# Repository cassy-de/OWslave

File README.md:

# OWslave
OneWire Slave DIY Module

 ATtiny 25, intern 8MHz
 PB4 als Autoincrement-Counters.A, low-aktiv (Pegel), alle 10 Sekunden ein Count
 PB3 ist abgehängt von Counters.B, dafür machen PB0 und PB1 den I2C-Bus für den SRF02 auf 

 lfuse 62
 hfuse DF
 efuse FF

-------------
Zur Firmware:
Die I2C-Libs werden zusätzlich eingebunden, die I2C-Adresse des SRF02 ist fix 0xE0, er wird mit cm als Rückgabewert programmiert. Die Interrupts von
PB3 und PB4 sind disabled, denn PB3 (Counters.B) wird nicht benötigt (ist Messwert des SRF02), und PB4 (Counters.A) wird in der main{} gepollt, dann 10 Sekunden Pause und wieder von vorne, also eigentlich straightforward gelöst. Die I2C-Routine sind atomar gesetzt, dass hier kein IRQ dazwischenfunkt. Somit kann es passieren, dass u.U. der OWFS/OWserver das Device nicht erreicht. Aber lieber in FHEM einen alten Messwert fortschreiben, als einen definitiv falschen eintragen. Achso, in der ISR sind die beiden Increments gelöscht. Und die Extra-Inits für den ATtiny2313 habe ich gleich aus dem Quellcode geschmissen, somit liest es sich etwas leichter.

-------------
OWServer Anzeige:

address 1DA2D984000102F3

counters.ALL 5, 136

counters.A 5

counters.B 136

crc8 F3

family 1D

id A2D984000102

Passt alles soweit, der Brenner lief testweise 55 Sekunden (counters.A ist 5), und bis zum Heizöl sind es  136 cm.

Viel Spass beim Testen.

cassy

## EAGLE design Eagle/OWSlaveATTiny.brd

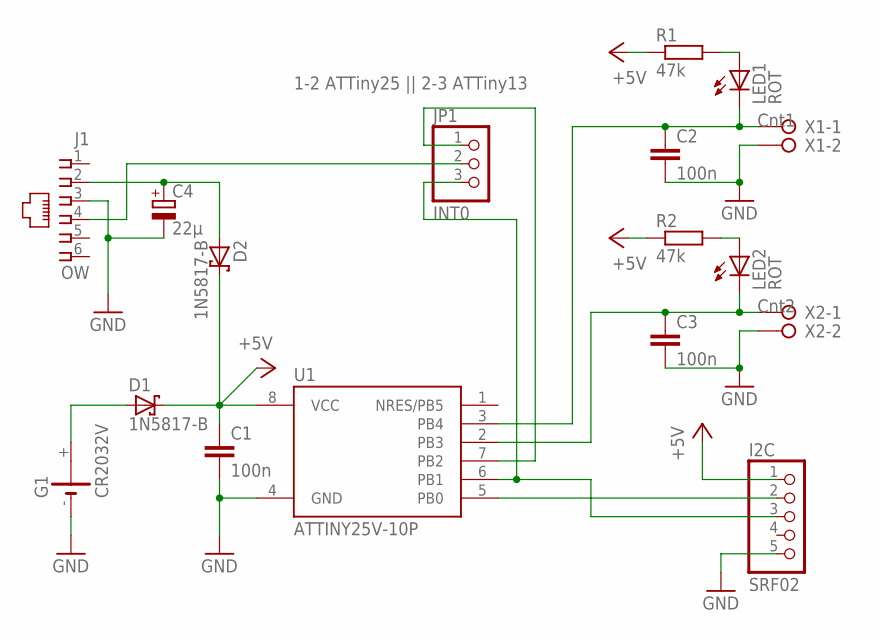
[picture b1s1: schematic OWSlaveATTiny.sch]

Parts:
C1, C2, C3: 100n; C050-025X075
C4: 22µ; E2,5-6E
D1, D2: 1N5817-B; DO41-7.6
G1: CR2032V
I2C: SRF02; 1X05
J1: OW; 520250-3
JP1: INT0; 1X03
LED1, LED2: ROT; LED5MM
R1, R2: 47k; 0204/7
U1: ATTINY25V-10P; PDIP08_300MIL
X1: Cnt1; W237-132
X2: Cnt2; W237-132

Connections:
+5V: C1.1, D1.C, D2.C, I2C.1, R1.1, R2.1, U1.8 (VCC)
GND: C1.2, C2.2, C3.2, C4.-, G1.-, I2C.5, J1.3, U1.4 (GND), X1.2, X2.2
unnamed: LED1.A, R1.2
unnamed: D1.A, G1.+
unnamed: J1.4, JP1.2
unnamed: C2.1, LED1.K (C), U1.3 (PB4), X1.1
unnamed: C3.1, LED2.K (C), U1.2 (PB3), X2.1
unnamed: I2C.3, JP1.3, U1.6 (PB1)
unnamed: JP1.1, U1.7 (PB2)
unnamed: I2C.2, U1.5 (PB0)
unnamed: C4.+, D2.A, J1.2
unnamed: LED2.A, R2.2

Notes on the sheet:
1-2 ATTiny25 || 2-3 ATTiny13

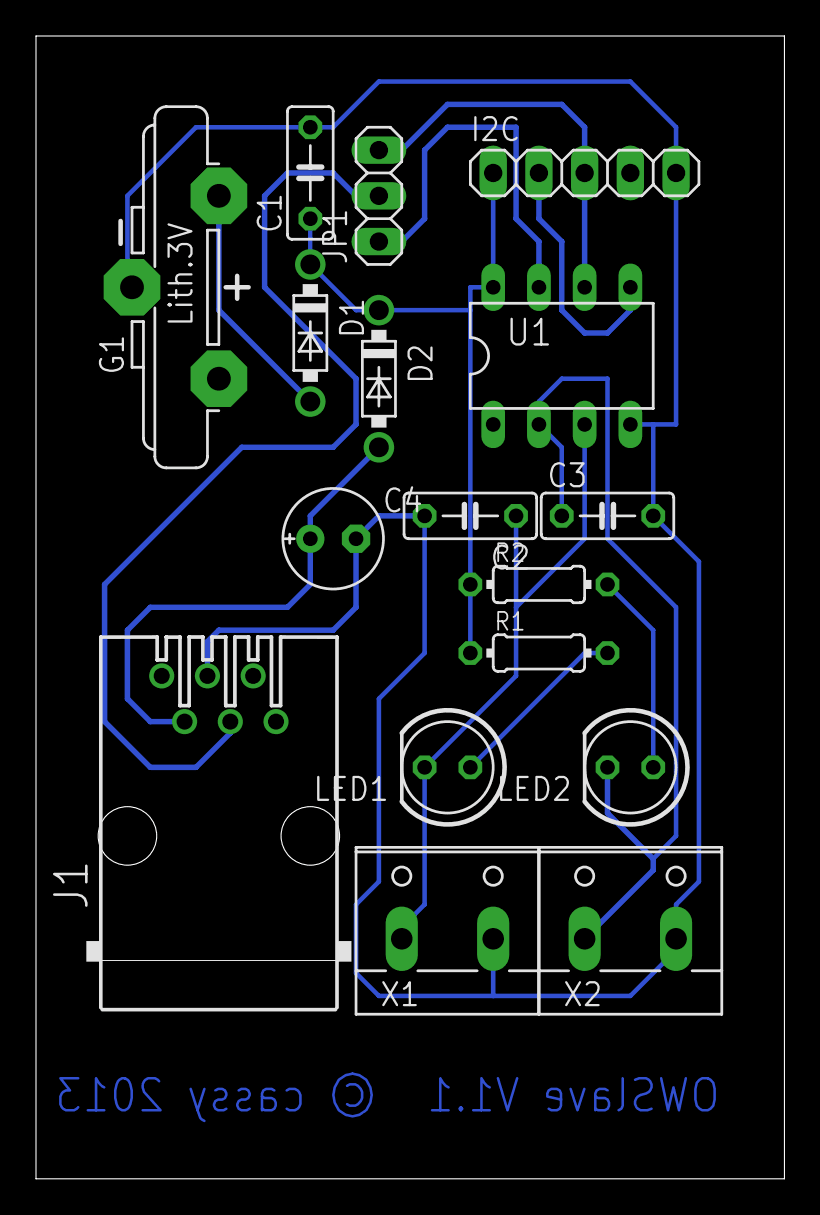
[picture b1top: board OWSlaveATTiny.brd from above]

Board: 2 copper layers, 41.6 x 63.5 mm, 17 parts (0 on the bottom side), 12 nets.

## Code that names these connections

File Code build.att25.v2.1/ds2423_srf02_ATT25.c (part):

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//VERSION 1.2 DS2423  for ATTINY2313 and ATTINY25
//Version 2.0 als DS2423 fuer ATtiny25 mit I2C-libs und Anbindung an SRF02 als counters.B
//Version 2.1 als DS2423 fuer ATtiny25 mit Sekunden-Zaehler counter.A, I2C-libs und Anbindung an SRF02 als counters.B
// PB0 - SDA
// PB1 - SCL
// PB2 - OW <- INT0 fixed
// PB3 - ( counters.A) als Gate fuer Counter.A-Sekundenimpulse 
// PB4 - ( counters.B) unused, nun als Ausgang fuer die Impuls-LED

#include <avr/io.h>
#include <avr/interrupt.h>
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#define LED_EIN OW_DDR|=OW_PINN;OW_PORT&=~OW_PORTN;  //set LED line to low
#define LED_AUS {OW_DDR&=~OW_PINN;}  //set LED pin as input -> LED aus

// OW_PORT Pin 7  - PB2
//OW Pin
#define OW_PORT PORTB //1 Wire Port
#define OW_PIN PINB //1 Wire Pin as number
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				   GIMSK=(1<<INT0);  /*set direct GIMSK register*/ \
				   TCCR0B=(1<<CS00)|(1<<CS01); /*8mhz /64 couse 8 bit Timer interrupt every 8us*/

// PINB3 und PB4 werden nun gepollt für die Sekundengate-Zählerfunktion
// somit IRQ-Funktionen nicht benötigt				   
// #define PC_INT_ISR ISR(PCINT0_vect) { /*ATT25 with 0 by PCINT*/ \
//					if (((PINB&(1<<PINB3))==0)&&((istat&(1<<PINB3))==(1<<PINB3))) {	}		\
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	{
	// Start	Distance Measurement
	Counter0 = read_cm(SRF02_ADDRESS);
	if ((PINB&(1<<PINB4))==0)	// PB4 als Gate für den Sekundenzähler
		{
		Counter1++;
		LED_EIN;	// PB3 low LED ein
		}
    _delay_ms(500);
	LED_AUS;		// PB3 high LED aus
	_delay_ms(500);
	}
}	
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

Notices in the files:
Code build.att25.v2.1/ds2423_srf02_ATT25.c:
Copyright (C) 2012  Tobias Mueller mail (at) tobynet.de
This program is free software: you can redistribute it and/or modify
it under the terms of the GNU General Public License as published by
the Free Software Foundation, either version 3 of the License, or
any later version.
Eagle/OWSlaveATTiny.brd:
© cassy 2013
